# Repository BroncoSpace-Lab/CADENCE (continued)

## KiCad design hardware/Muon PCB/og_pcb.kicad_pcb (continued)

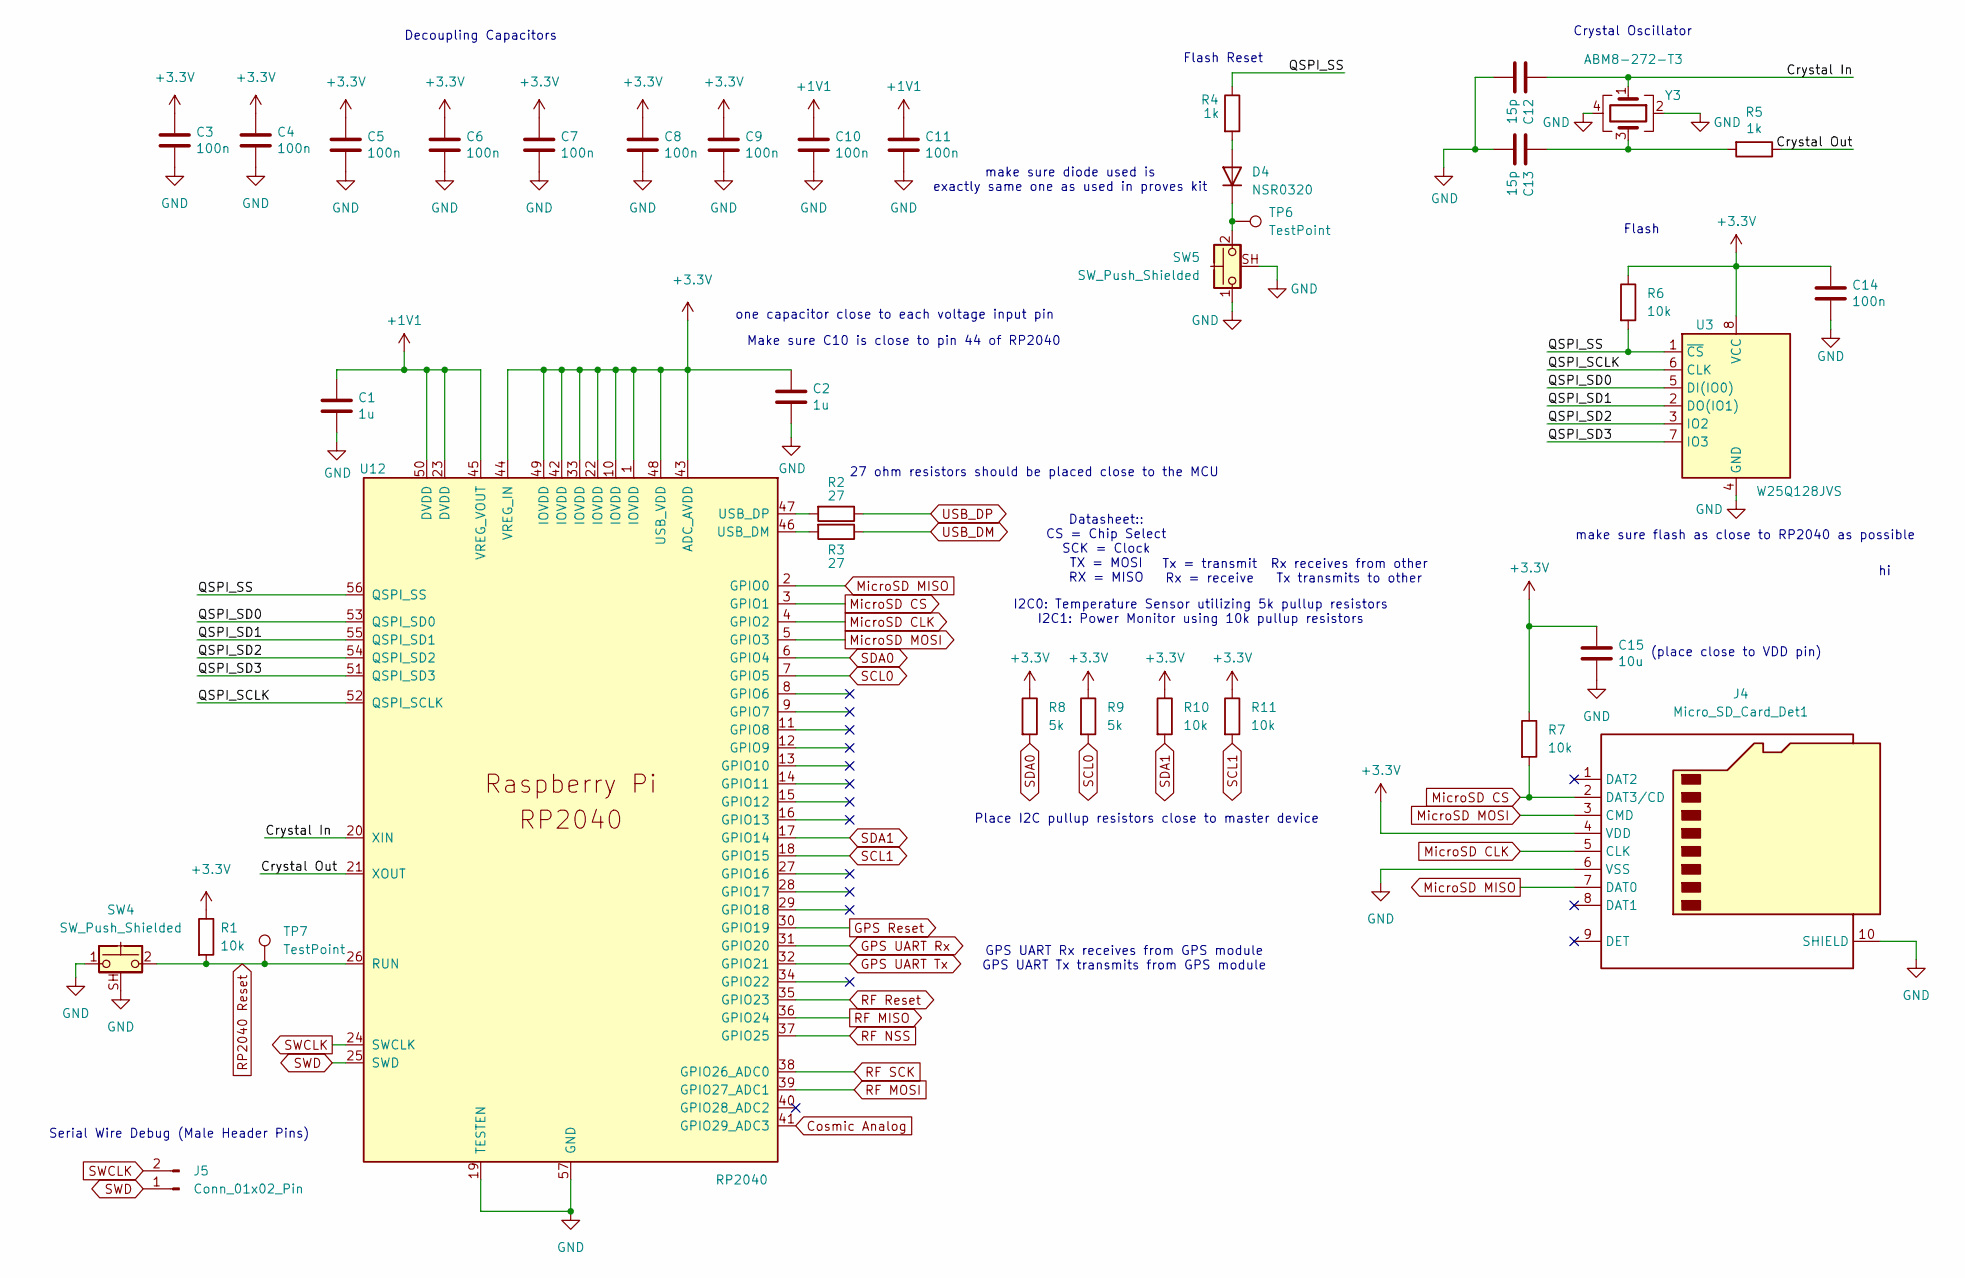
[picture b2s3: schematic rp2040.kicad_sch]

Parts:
C1, C2: 1u; C_0603_1608Metric
C3, C4, C5, C6, C7, C8, C9, C10, C11, C14: 100n; C_0402_1005Metric
C12, C13: 15p; C_0201_0603Metric
C15: 10u; C_0805_2012Metric
D4: NSR0320; D_SOD-323F
J4: Micro_SD_Card_Det1; microSD-503398-1892-1
J5: Conn_01x02_Pin; PinHeader_1x02_P1.00mm_Vertical
R1, R6, R7, R10, R11: 10k; R_0402_1005Metric
R2, R3: 27; R_0402_1005Metric
R4, R5: 1k; R_0402_1005Metric
R8, R9: 5k; R_0402_1005Metric
SW4, SW5: SW_Push_Shielded; SW_Push_1P1T-SH_NO_CK_KMR2xxG
TP6, TP7: TestPoint; TestPoint_Loop_D1.80mm_Drill1.0mm_Beaded
U3: W25Q128JVS; SOIC_208MIL_WIN
U12: RP2040; QFN-56-1EP_7x7mm_P0.4mm_EP3.2x3.2mm
Y3: ABM8-272-T3; Crystal_SMD_3225-4Pin_3.2x2.5mm

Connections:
+1V1: C1.1, C10.1, C11.1, U12.23 (DVDD), U12.45 (VREG_VOUT), U12.50 (DVDD)
+3.3V: C2.1, C3.1, C4.1, C5.1, C6.1, C7.1, C8.1, C9.1, C14.1, C15.1, J4.4 (VDD), R1.1, R6.1, R7.1, R8.1, R9.1, R10.1, R11.1, U3.8 (VCC), U12.1 (IOVDD), U12.10 (IOVDD), U12.22 (IOVDD), U12.33 (IOVDD), U12.42 (IOVDD), U12.43 (ADC_AVDD), U12.44 (VREG_IN), U12.48 (USB_VDD), U12.49 (IOVDD); also elsewhere on the board
/RP2040 MCU/Crystal In: C12.1, U12.20 (XIN), Y3.1
/RP2040 MCU/Crystal Out: R5.1, U12.21 (XOUT)
/RP2040 MCU/QSPI_SCLK: U3.6 (CLK), U12.52 (QSPI_SCLK)
/RP2040 MCU/QSPI_SD0: U3.5 (DI(IO0)), U12.53 (QSPI_SD0)
/RP2040 MCU/QSPI_SD1: U3.2 (DO(IO1)), U12.55 (QSPI_SD1)
/RP2040 MCU/QSPI_SD2: U3.3 (IO2), U12.54 (QSPI_SD2)
/RP2040 MCU/QSPI_SD3: U3.7 (IO3), U12.51 (QSPI_SD3)
/RP2040 MCU/QSPI_SS: R4.1, R6.2, U3.1 (~CS), U12.56 (QSPI_SS)
Cosmic Analog: U12.41 (GPIO29_ADC3); also elsewhere on the board
GND: C1.2, C2.2, C3.2, C4.2, C5.2, C6.2, C7.2, C8.2, C9.2, C10.2, C11.2, C12.2, C13.2, C14.2, C15.2, J4.6 (VSS), J4.10 (SHIELD), SW4.1, SW4.SH (B), SW5.1, SW5.SH (B), U3.4 (GND), U12.19 (TESTEN), U12.57 (GND), Y3.2, Y3.4; also elsewhere on the board
GPS Reset: U12.30 (GPIO19); also elsewhere on the board
GPS UART Rx: U12.31 (GPIO20); also elsewhere on the board
GPS UART Tx: U12.32 (GPIO21); also elsewhere on the board
MicroSD CLK: J4.5 (CLK), U12.4 (GPIO2)
MicroSD CS: J4.2 (DAT3/CD), R7.2, U12.3 (GPIO1)
MicroSD MISO: J4.7 (DAT0), U12.2 (GPIO0)
MicroSD MOSI: J4.3 (CMD), U12.5 (GPIO3)
unnamed: C13.1, R5.2, Y3.3
unnamed: D4.2 (A), R4.2
unnamed: D4.1 (K), SW5.2, TP6.1
unnamed: R3.2, U12.46 (USB_DM)
unnamed: R2.2, U12.47 (USB_DP)
RF MISO: U12.36 (GPIO24); also elsewhere on the board
RF MOSI: U12.39 (GPIO27_ADC1); also elsewhere on the board
RF NSS: U12.37 (GPIO25); also elsewhere on the board
RF Reset: U12.35 (GPIO23); also elsewhere on the board
RF SCK: U12.38 (GPIO26_ADC0); also elsewhere on the board
RP2040 Reset: R1.2, SW4.2, TP7.1, U12.26 (RUN)
SCL0: R9.2, U12.7 (GPIO5); also elsewhere on the board
SCL1: R11.2, U12.18 (GPIO15); also elsewhere on the board
SDA0: R8.2, U12.6 (GPIO4); also elsewhere on the board
SDA1: R10.2, U12.17 (GPIO14); also elsewhere on the board
SWCLK: J5.2, U12.24 (SWCLK)
SWD: J5.1, U12.25 (SWD)
USB_DM: R3.1; also elsewhere on the board
USB_DP: R2.1; also elsewhere on the board

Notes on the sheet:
Place I2C pullup resistors close to master device
Make sure C10 is close to pin 44 of RP2040
Rx receives from other Tx transmits to other
Tx = transmit Rx = receive
27 ohm resistors should be placed close to the MCU
Flash
one capacitor close to each voltage input pin
Decoupling Capacitors
Serial Wire Debug (Male Header Pins)
make sure flash as close to RP2040 as possible
(place close to VDD pin)
I2C0: Temperature Sensor utilizing 5k pullup resistors I2C1: Power Monitor using 10k pullup resistors
Crystal Oscillator
GPS UART Rx receives from GPS module GPS UART Tx transmits from GPS module
Datasheet:: CS = Chip Select SCK = Clock TX = MOSI RX = MISO
make sure diode used is exactly same one as used in proves kit
Flash Reset

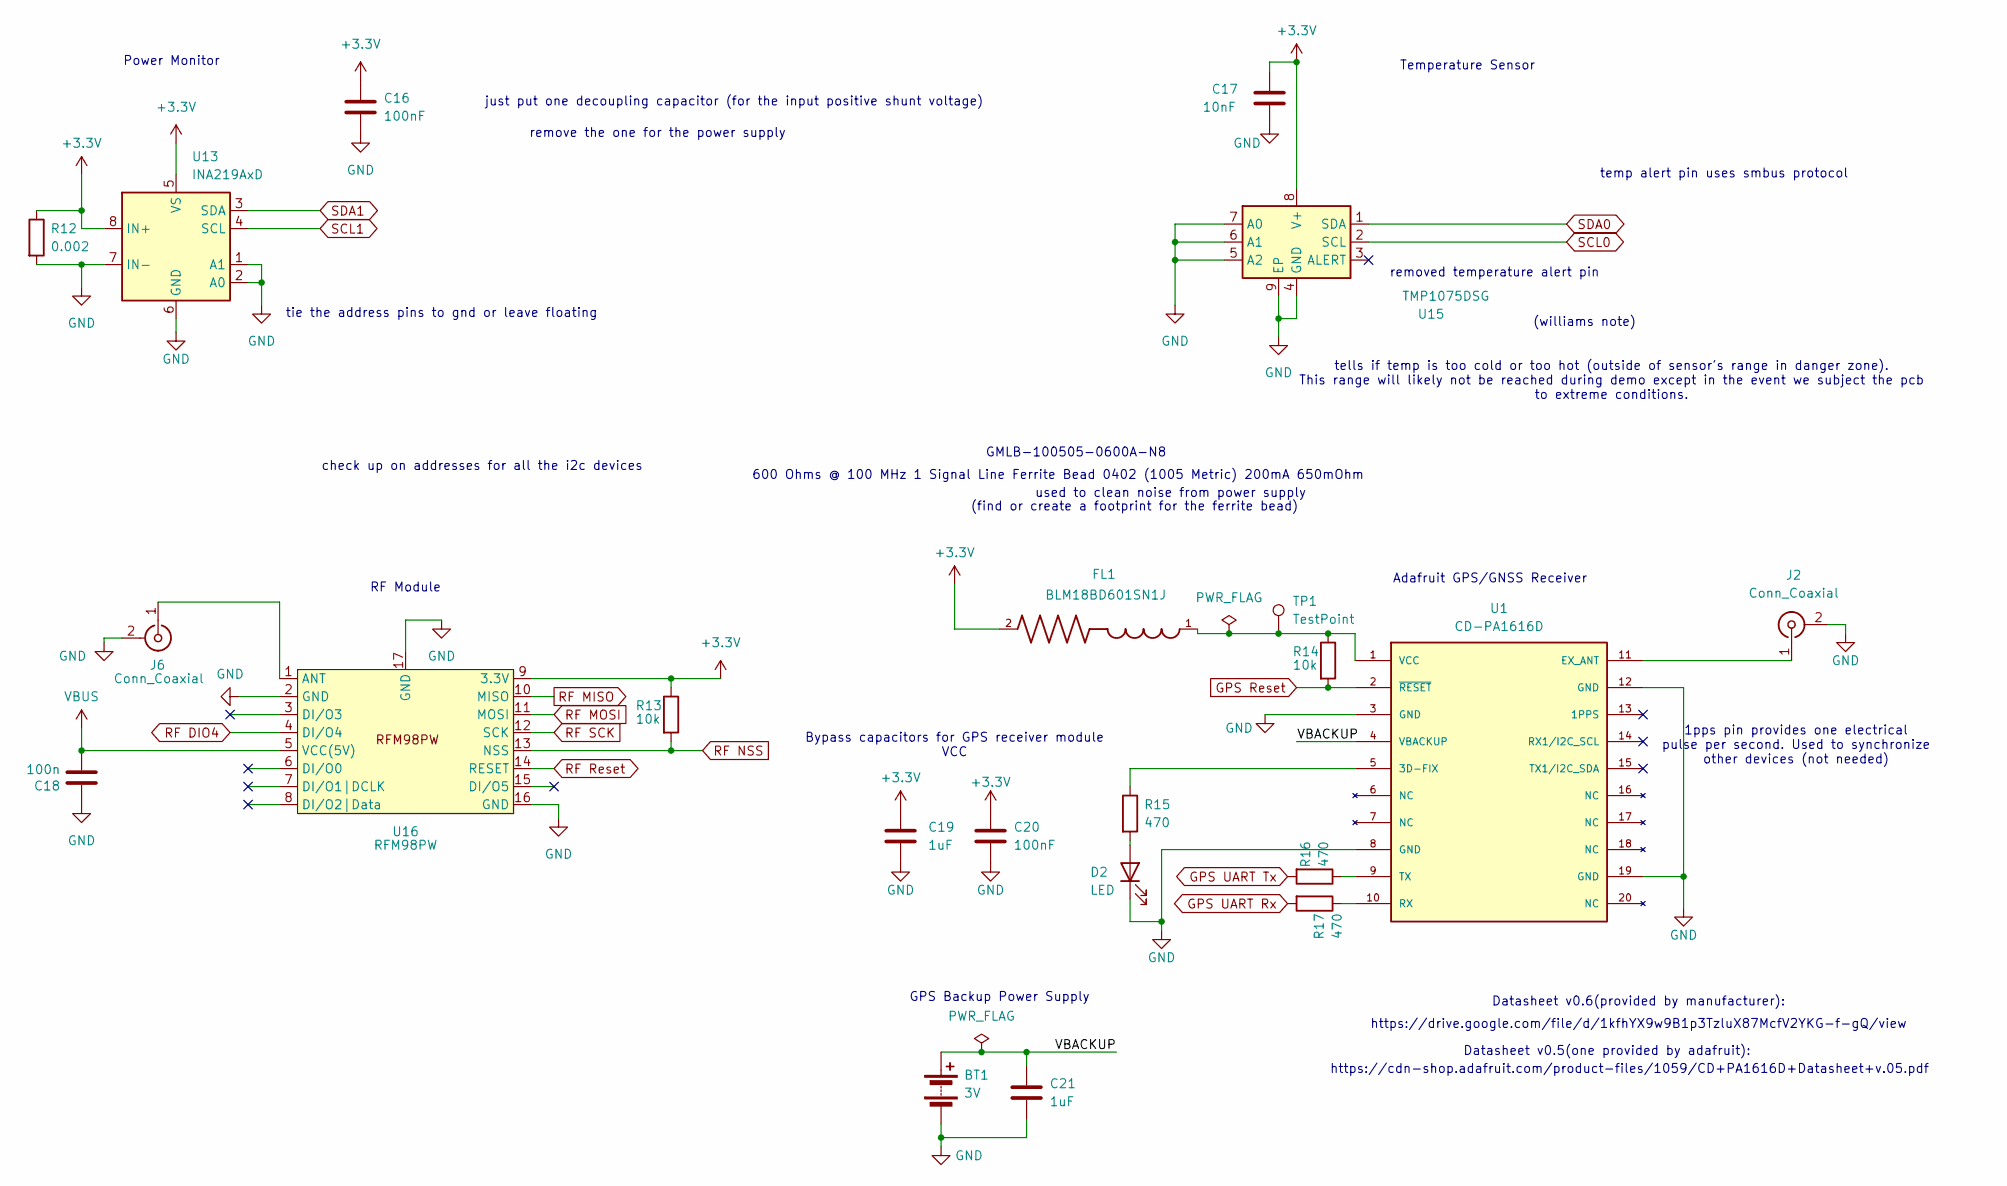
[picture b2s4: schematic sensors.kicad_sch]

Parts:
BT1: 3V; BatteryHolder_Keystone_1058_1x2032
C16, C20: 100nF; C_0402_1005Metric
C17: 10nF; C_0402_1005Metric
C18: 100n; C_0402_1005Metric
C19, C21: 1uF; C_0603_1608Metric
D2: LED; LED_0402_1005Metric
FL1: BLM18BD601SN1J; BEADC1608X95N
J2, J6: Conn_Coaxial; MMCX_Molex_73415-1471_Vertical
R12: 0.002; R_2512_6332Metric
R13, R14: 10k; R_0402_1005Metric
R15, R16, R17: 470; R_0603_1608Metric
TP1: TestPoint; TestPoint_Loop_D1.80mm_Drill1.0mm_Beaded
U1: CD-PA1616D; PARTREV V.06
U13: INA219AxD; SOIC-8_3.9x4.9mm_P1.27mm
U15: TMP1075DSG; WSON-8-1EP_2x2mm_P0.5mm_EP0.9x1.6mm_ThermalVias
U16: RFM98PW

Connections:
+3.3V: C16.1, C17.1, C19.1, C20.1, FL1.2, R12.1, R13.1, U13.5 (VS), U13.8 (IN+), U15.8 (V+), U16.9 (3.3V); also elsewhere on the board
/Sensors/VBACKUP: BT1.1 (+), C21.1, U1.4 (VBACKUP)
GND: BT1.2 (-), C16.2, C17.2, C18.1, C19.2, C20.2, C21.2, D2.1 (K), J2.2 (Ext), J6.2 (Ext), R12.2, U1.3 (GND), U1.8 (GND), U1.12 (GND), U1.19 (GND), U13.1 (A1), U13.2 (A0), U13.6 (GND), U13.7 (IN-), U15.4 (GND), U15.5 (A2), U15.6 (A1), U15.7 (A0), U15.9 (EP), U16.2 (GND), U16.16 (GND), U16.17 (GND); also elsewhere on the board
GPS Reset: R14.2, U1.2 (~RESET); also elsewhere on the board
GPS UART Rx: R17.2; also elsewhere on the board
GPS UART Tx: R16.2; also elsewhere on the board
unnamed: D2.2 (A), R15.2
unnamed: J2.1 (In), U1.11 (EX_ANT)
unnamed: J6.1 (In), U16.1 (ANT)
unnamed: R15.1, U1.5 (3D-FIX)
unnamed: R17.1, U1.10 (RX)
unnamed: R16.1, U1.9 (TX)
unnamed: FL1.1, R14.1, TP1.1, U1.1 (VCC)
RF DIO4: U16.4 (DI/O4)
RF MISO: U16.10 (MISO); also elsewhere on the board
RF MOSI: U16.11 (MOSI); also elsewhere on the board
RF NSS: R13.2, U16.13 (NSS); also elsewhere on the board
RF Reset: U16.14 (RESET); also elsewhere on the board
RF SCK: U16.12 (SCK); also elsewhere on the board
SCL0: U15.2 (SCL); also elsewhere on the board
SCL1: U13.4 (SCL); also elsewhere on the board
SDA0: U15.1 (SDA); also elsewhere on the board
SDA1: U13.3 (SDA); also elsewhere on the board
VBUS: C18.2, U16.5 (VCC(5V)); also elsewhere on the board

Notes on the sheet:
temp alert pin uses smbus protocol
RF Module
GPS Backup Power Supply
tells if temp is too cold or too hot (outside of sensor's range in danger zone). This range will likely not be reached during demo except in the event we subject the pcb to extreme conditions.
Power Monitor
removed temperature alert pin
GMLB-100505-0600A-N8
https://drive.google.com/file/d/1kfhYX9w9B1p3TzluX87McfV2YKG-f-gQ/view
Datasheet v0.5(one provided by adafruit):
(williams note)
Temperature Sensor
600 Ohms @ 100 MHz 1 Signal Line Ferrite Bead 0402 (1005 Metric) 200mA 650mOhm
Datasheet v0.6(provided by manufacturer):
check up on addresses for all the i2c devices
1pps pin provides one electrical pulse per second. Used to synchronize other devices (not needed)
used to clean noise from power supply
just put one decoupling capacitor (for the input positive shunt voltage)
(find or create a footprint for the ferrite bead)
Bypass capacitors for GPS receiver module VCC
remove the one for the power supply
tie the address pins to gnd or leave floating
Adafruit GPS/GNSS Receiver
https://cdn-shop.adafruit.com/product-files/1059/CD+PA1616D+Datasheet+v.05.pdf

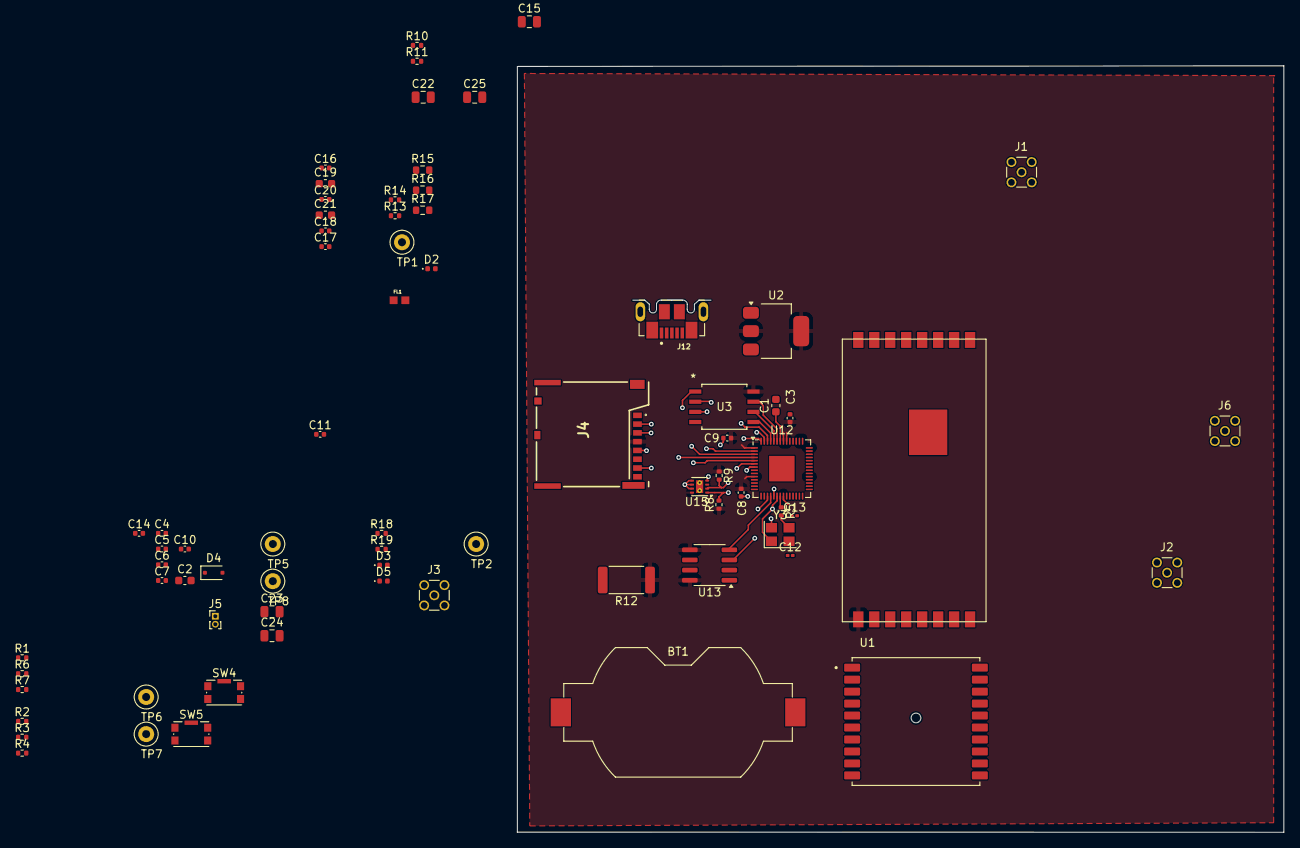
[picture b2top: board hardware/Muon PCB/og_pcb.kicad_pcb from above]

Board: 4 copper layers, 96.0 x 96.0 mm, 73 parts (0 on the bottom side), 49 nets.

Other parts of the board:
C25: 10u; C_0805_2012Metric
J3: Conn_Coaxial_Power; MMCX_Molex_73415-1471_Vertical

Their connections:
GND: C25.2; also elsewhere on the board
VBUS: C25.1, J3.1 (In); also elsewhere on the board

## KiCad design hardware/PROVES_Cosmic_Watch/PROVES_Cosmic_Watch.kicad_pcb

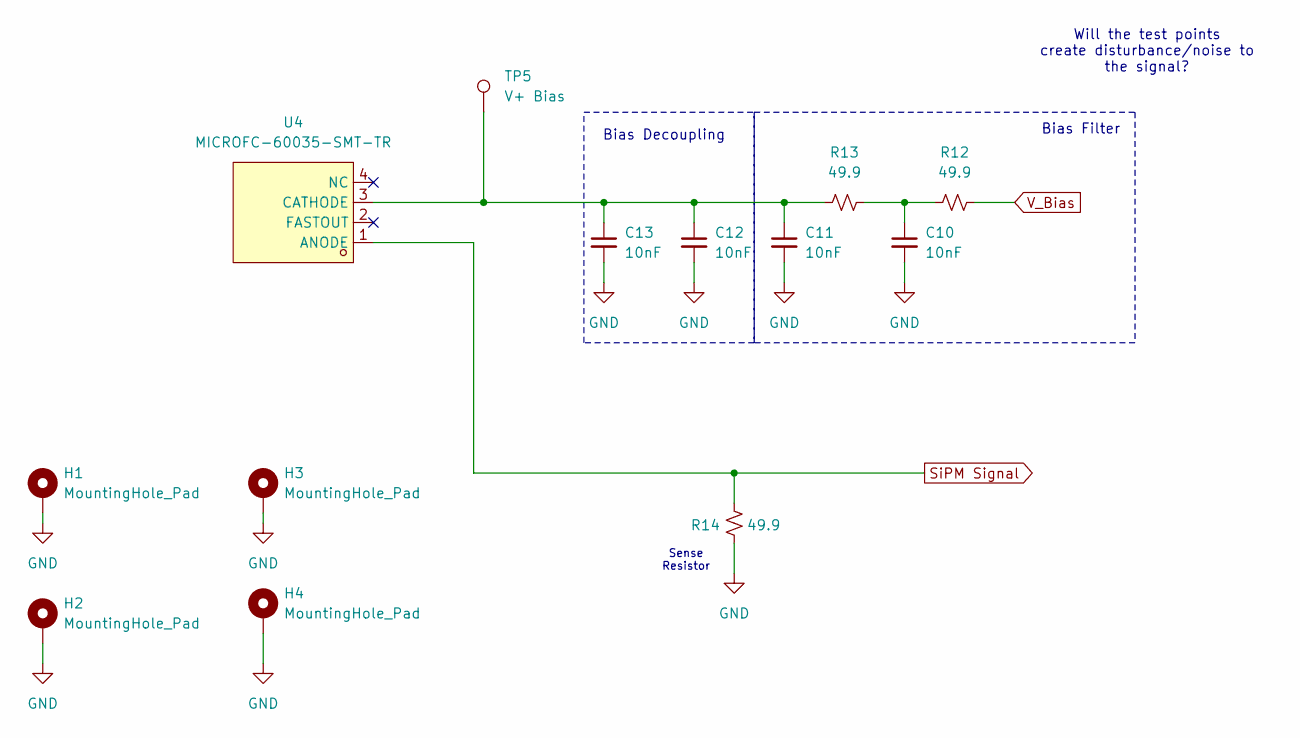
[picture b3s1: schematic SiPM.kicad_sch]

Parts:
C10, C11, C12, C13: 10nF; C_0805_2012Metric
H1, H2, H3, H4: MountingHole_Pad; MountingHole_2.7mm_M2.5
R12, R13, R14: 49.9; R_0805_2012Metric
TP5: V+ Bias; TestPoint_Keystone_5000-5004_Miniature
U4: MICROFC-60035-SMT-TR; OPTO-SMD_4P-MICROFC-60035-SMT-TR; LCSC Part C603293

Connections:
GND: C10.2, C11.2, C12.2, C13.2, H1.1, H2.1, H3.1, H4.1, R14.2; also elsewhere on the board
unnamed: C10.1, R12.1, R13.2
unnamed: C11.1, C12.1, C13.1, R13.1, TP5.1, U4.3 (CATHODE)
SiPM Signal: R14.1, U4.1 (ANODE); also elsewhere on the board
V_Bias: R12.2; also elsewhere on the board

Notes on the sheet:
Bias Filter
Bias Decoupling
Sense Resistor
Will the test points create disturbance/noise to the signal?

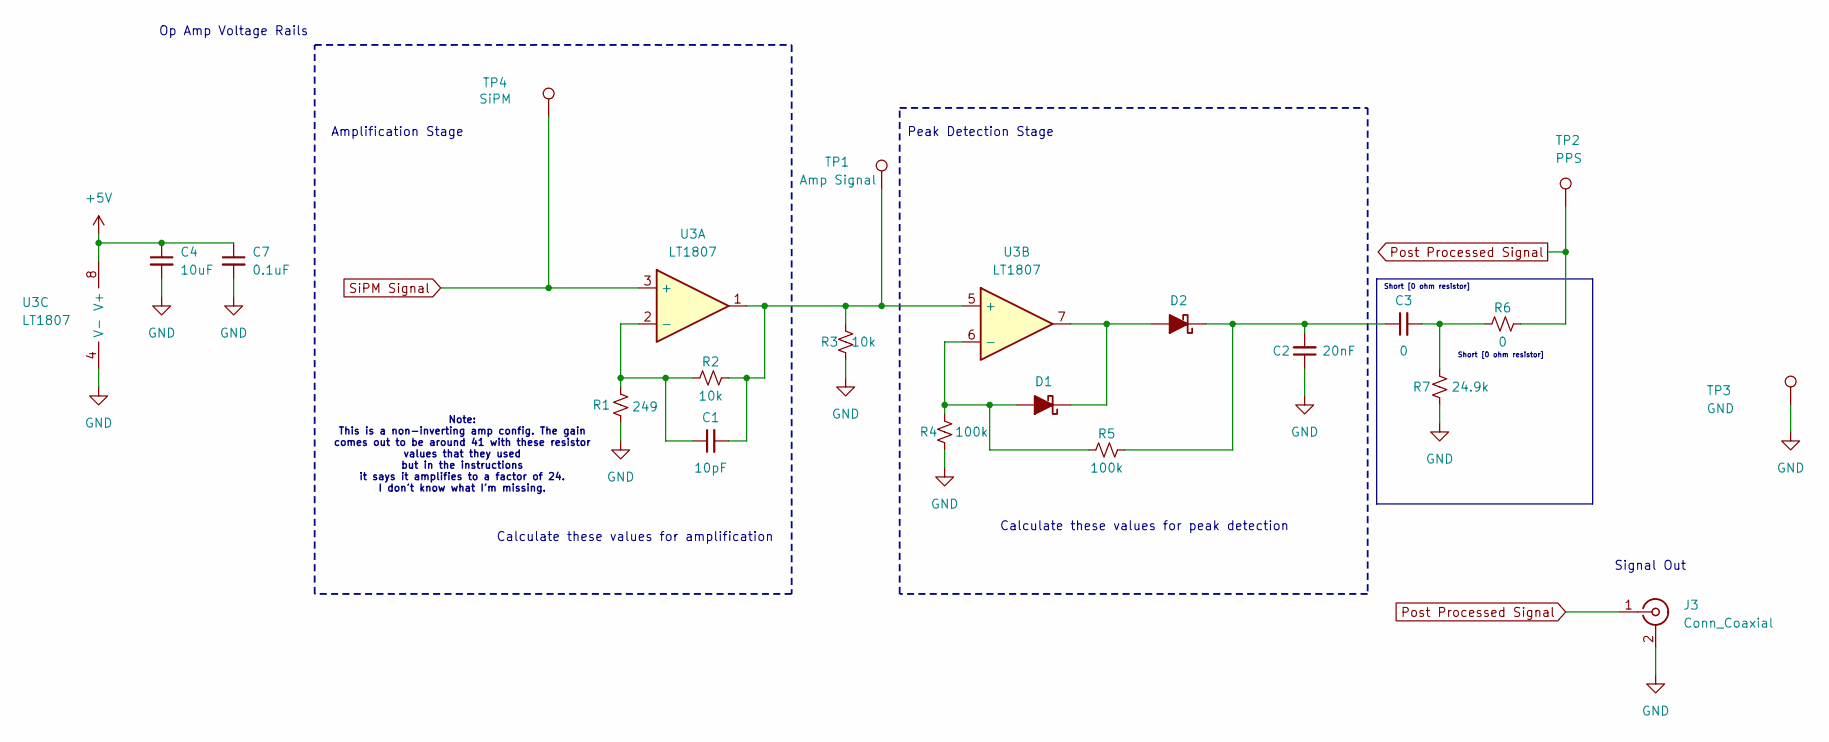
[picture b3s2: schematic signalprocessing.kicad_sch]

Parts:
C1: 10pF; C_0805_2012Metric
C2: 20nF; C_0805_2012Metric
C3: 0; R0805
C4: 10uF; C_0805_2012Metric
C7: 0.1uF; C_0805_2012Metric
D1, D2: SOD-123_L2.8-W1.8-LS3.7-RD
J3: Conn_Coaxial; SMA_Amphenol_901-144_Vertical
R1: 249; R_0805_2012Metric
R2, R3: 10k; R_0805_2012Metric
R4, R5: 100k; R_0805_2012Metric
R6: 0; R0805
R7: 24.9k; R_0805_2012Metric
TP1: Amp Signal; TestPoint_Keystone_5000-5004_Miniature
TP2: PPS; TestPoint_Keystone_5000-5004_Miniature
TP3: GND; TestPoint_Keystone_5000-5004_Miniature
TP4: SiPM; TestPoint_Keystone_5000-5004_Miniature
U3: LT1807; SOIC-8_L5.0-W4.0-P1.27-LS6.0-BL

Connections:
+5V: C4.1, C7.1, U3.8 (V+); also elsewhere on the board
GND: C2.1, C4.2, C7.2, J3.2 (Ext), R1.2, R3.1, R4.1, R7.1, TP3.1, U3.4 (V-); also elsewhere on the board
unnamed: C3.2, R6.1, R7.2
unnamed: D1.2 (A), R4.2, R5.1, U3.6 (-)
unnamed: D1.1 (K), D2.2 (A), U3.7
unnamed: C2.2, C3.1, D2.1 (K), R5.2
unnamed: C1.1, R1.1, R2.1, U3.2 (-)
unnamed: C1.2, R2.2, R3.2, TP1.1, U3.1, U3.5 (+)
Post Processed Signal: J3.1 (In), R6.2, TP2.1
SiPM Signal: TP4.1, U3.3 (+); also elsewhere on the board

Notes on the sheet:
Calculate these values for amplification
Calculate these values for peak detection
Op Amp Voltage Rails
Note: This is a non-inverting amp config. The gain comes out to be around 41 with these resistor values that they used but in the instructions it says it amplifies to a factor of 24. I don't know what I'm missing.
Amplification Stage
Signal Out
Short [0 ohm resistor]
Peak Detection Stage

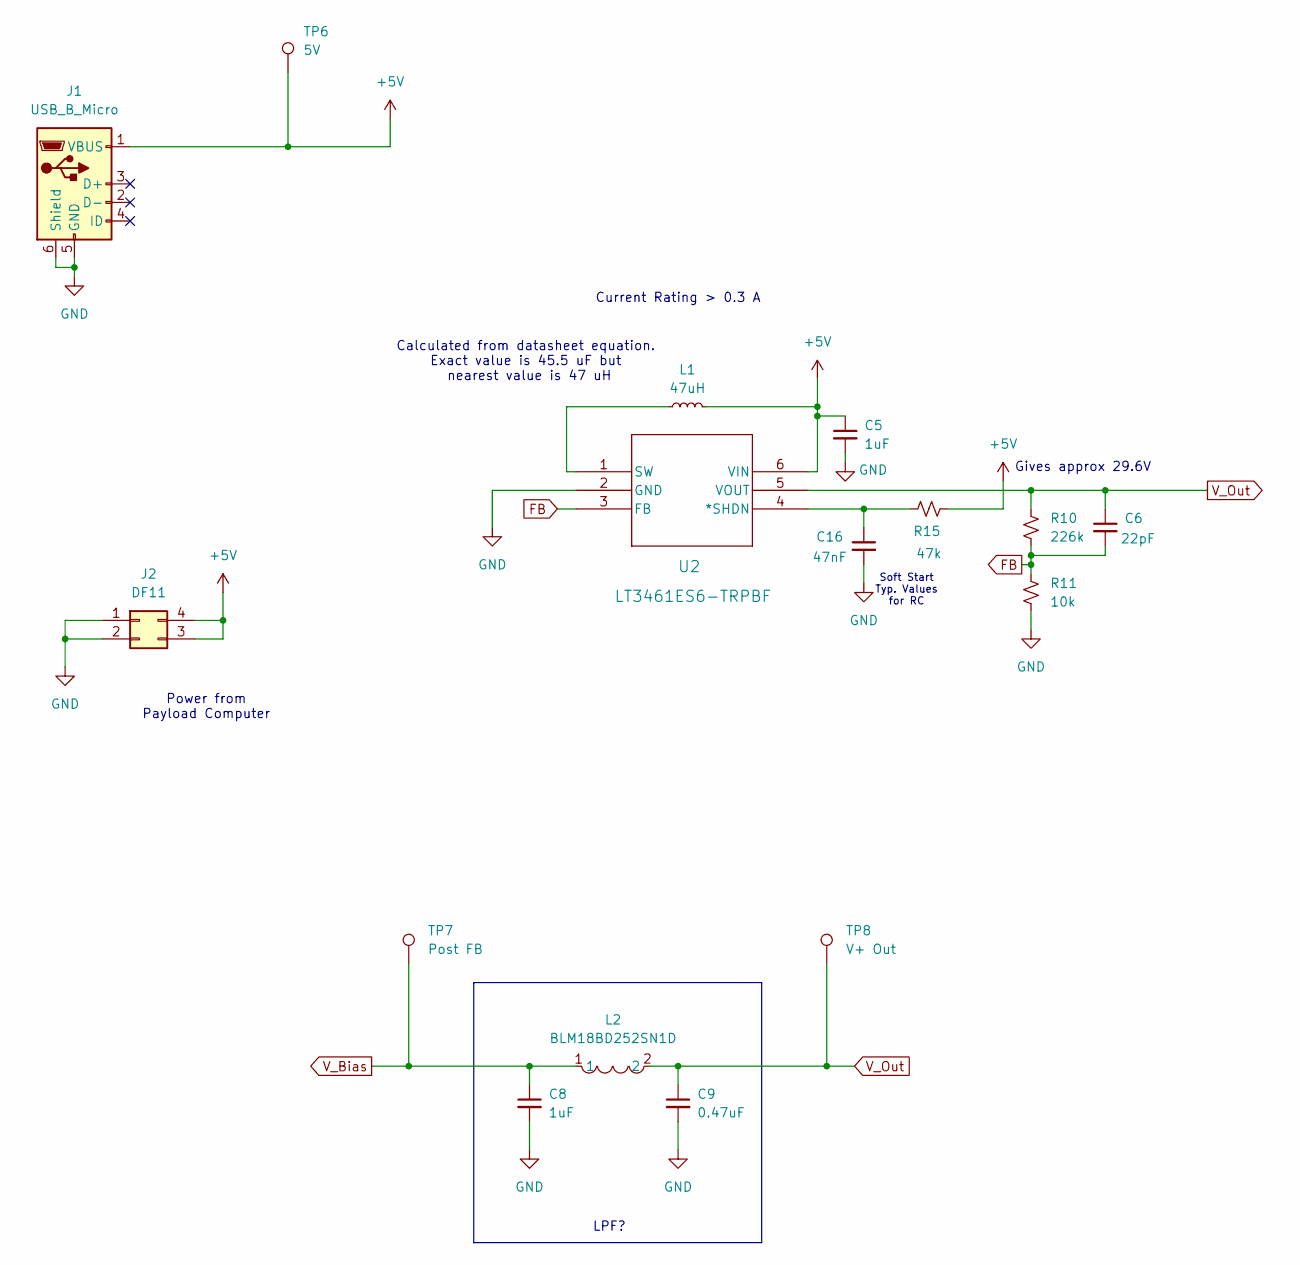
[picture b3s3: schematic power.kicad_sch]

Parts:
C5, C8: 1uF; C_0805_2012Metric
C6: 22pF; C_0805_2012Metric
C9: 0.47uF; C_0805_2012Metric
C16: 47nF; C_0805_2012Metric
J1: USB_B_Micro; MICRO-USB-SMD_5P-P0.65-H-F_105164-0001
J2: DF11; CONN-TH_DF11-4DP-2DSA-08
L1: 47uH; L1210
L2: BLM18BD252SN1D; L0603; LCSC Part C77668
R10: 226k; R_0805_2012Metric
R11: 10k; R_0805_2012Metric
R15: 47k; R_0805_2012Metric
TP6: 5V; TestPoint_Keystone_5000-5004_Miniature
TP7: Post FB; TestPoint_Keystone_5000-5004_Miniature
TP8: V+ Out; TestPoint_Keystone_5000-5004_Miniature
U2: LT3461ES6-TRPBF; TSOT-23_S6_LIT

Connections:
+5V: C5.1, J1.1 (VBUS), J2.3, J2.4, L1.2, R15.2, TP6.1, U2.6 (VIN); also elsewhere on the board
FB: C6.2, R10.2, R11.1, U2.3 (FB)
GND: C5.2, C8.2, C9.2, C16.2, J1.5 (GND), J1.6 (Shield), J2.1, J2.2, R11.2, U2.2 (GND); also elsewhere on the board
unnamed: C16.1, R15.1, U2.4 (*SHDN)
unnamed: L1.1, U2.1 (SW)
V_Bias: C8.1, L2.1, TP7.1; also elsewhere on the board
V_Out: C6.1, C9.1, L2.2, R10.1, TP8.1, U2.5 (VOUT)

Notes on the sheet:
Soft Start Typ. Values for RC
Gives approx 29.6V
Current Rating > 0.3 A
LPF?
Power from Payload Computer
Calculated from datasheet equation. Exact value is 45.5 uF but nearest value is 47 uH

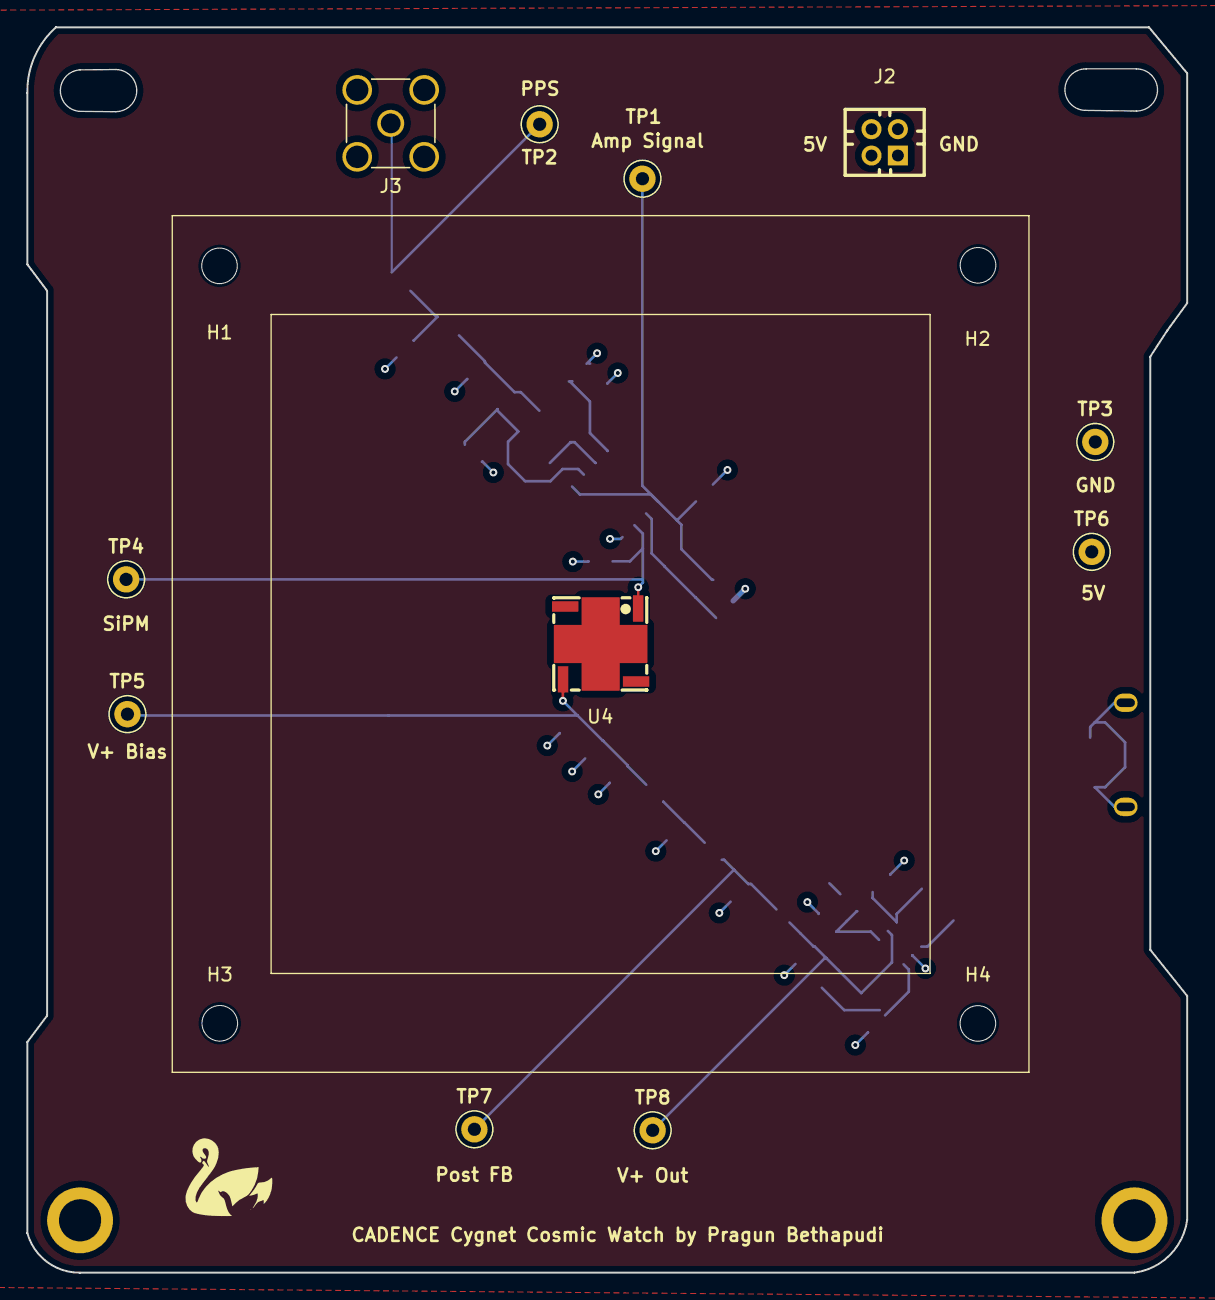
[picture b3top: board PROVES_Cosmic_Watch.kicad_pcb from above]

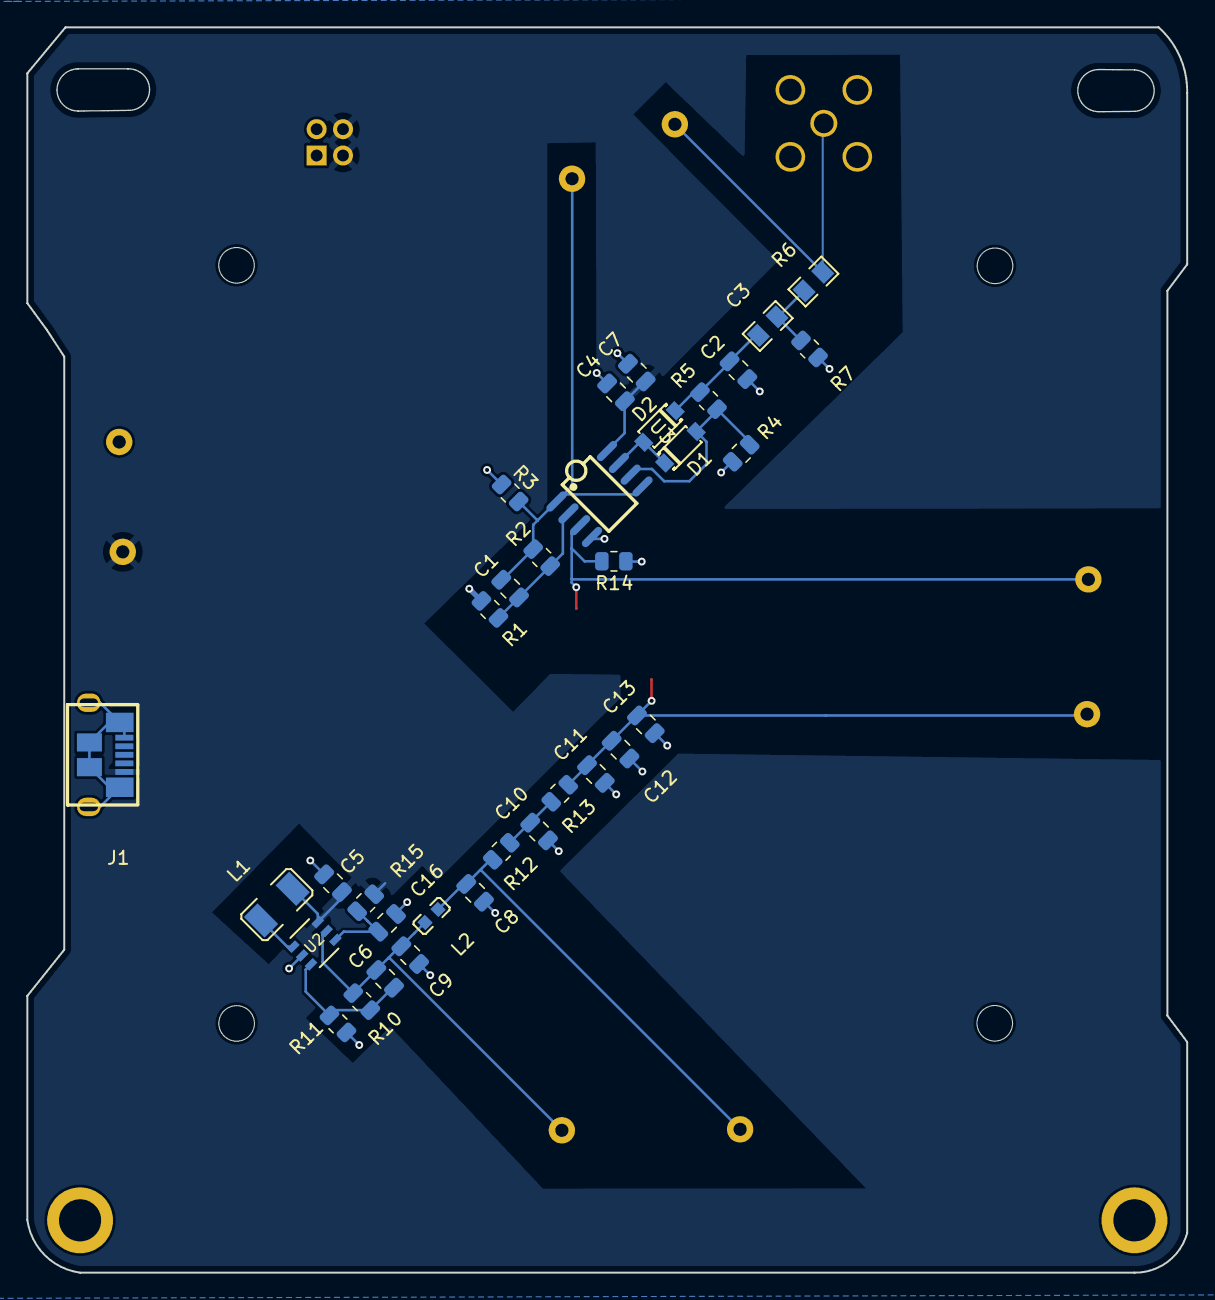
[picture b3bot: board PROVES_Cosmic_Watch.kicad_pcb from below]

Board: 4 copper layers, 88.0 x 94.5 mm, 49 parts (34 on the bottom side), 17 nets.

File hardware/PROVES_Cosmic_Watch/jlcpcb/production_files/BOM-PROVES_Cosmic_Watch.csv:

Comment,Designator,Footprint,LCSC,Quantity
22pF,C6,C_0805_2012Metric,C105623,1
1uF,"C5,C8",C_0805_2012Metric,C106838,2
0.47uF,C9,C_0805_2012Metric,C106843,1
47nF,C16,C_0805_2012Metric,C107154,1
47k,R15,R_0805_2012Metric,C126351,1
49.9,"R12,R13,R14",R_0805_2012Metric,C132320,3
10k,"R11,R2,R3",R_0805_2012Metric,C140868,3
24.9k,R7,R_0805_2012Metric,C155691,1
DF11,J2,CONN-TH_DF11-4DP-2DSA-08,C185144,1
20nF,C2,C_0805_2012Metric,C1853321,1
~,"D1,D2",SOD-123_L2.8-W1.8-LS3.7-RD,C21353,2
226k,R10,R_0805_2012Metric,C228638,1
USB_B_Micro,J1,MICRO-USB-SMD_5P-P0.65-H-F_105164-0001,C234179,1
GND,TP3,TestPoint_Keystone_5000-5004_Miniature,C238122,1
Amp Signal,"TP1,TP2,TP4,TP7",TestPoint_Keystone_5000-5004_Miniature,C238123,4
249,R1,R_0805_2012Metric,C276301,1
10uF,C4,C_0805_2012Metric,C307525,1
Conn_Coaxial,J3,SMA_Amphenol_901-144_Vertical,C376663,1
10pF,C1,C_0805_2012Metric,C519954,1
V+ Bias,"TP5,TP6,TP8",TestPoint_Keystone_5000-5004_Miniature,C5199900,3
MICROFC-60035-SMT-TR,U4,OPTO-SMD_4P-MICROFC-60035-SMT-TR,C603293,1
LT1807,U3,SOIC-8_L5.0-W4.0-P1.27-LS6.0-BL,C665378,1
LT3461ES6-TRPBF,U2,TSOT-23_S6_LIT,C670573,1
47uH,L1,L1210,C701189,1
0.1uF,C7,C_0805_2012Metric,C77082,1
BLM18BD252SN1D,L2,L0603,C77668,1
10nF,"C10,C11,C12,C13",C_0805_2012Metric,C83170,4
0,"C3,R6",R0805,C96345,2
100k,"R4,R5",R_0805_2012Metric,C96346,2
